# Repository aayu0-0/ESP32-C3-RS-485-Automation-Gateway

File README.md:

# ESP32-C3 RS-485 Automation Gateway

A compact, modular automation gateway designed around the **Seeed Studio XIAO ESP32-C3**, featuring RS-485 communication and a MikroE mikroBUS-compatible form factor.

This project focuses on developing a practical hardware platform for industrial communication and automation applications through iterative PCB design and prototyping.

## Project Overview

The project consists of three PCB design iterations (V1, V2 and V3), each introducing refinements to the schematic, component selection, power management, PCB layout and overall hardware integration.

The latest design uses the XIAO ESP32-C3 and follows a compact layout intended to fit the CEB-35/CEBV-35 enclosure.

## Hardware Specifications

- **Microcontroller:** Seeed Studio XIAO ESP32-C3
- **Communication:** RS-485
- **Expansion Interface:** MikroE mikroBUS form factor
- **Enclosure Compatibility:** CEB-35 / CEBV-35
- **PCB Design Software:** KiCad

## Design Iterations

### V1 – Initial Prototype
- Initial schematic and PCB development.
- RS-485 communication interface.
- Initial PCB layout and Gerber generation.

### V2 – Hardware Refinement
- Revised schematic and component selection.
- Improvements to power-related circuitry.
- Refinements to the RS-485 interface.
- Updated PCB design.

### V3 – Refined Design
- Integration of the Seeed Studio XIAO ESP32-C3.
- Refined PCB layout and component placement.
- Compact form factor.
- Enclosure-oriented design for CEB-35/CEBV-35.

## Repository Structure

```text
Home_Automation_Bengaluru/
│
├── V1/
│   ├── Schematic/
│   ├── PCB/
│   └── Gerbers/
│
├── V2/
│   ├── Schematic/
│   ├── PCB/
│   └── Manufacturing/
│
├── V3/
│   ├── Schematic/
│   ├── PCB/
│   └── Manufacturing/
│
├── Libraries/
│   └── Custom KiCad footprints and symbols
│
├── Datasheets/
│
└── README.md
```

*Directory names may vary according to the actual repository organization.*

## Software and Tools

- KiCad – Schematic capture and PCB layout.
- ESP32-C3 – Embedded processing platform.
- Git – Version control and project management.

## Getting Started

1. Clone the repository:

   ```bash
   git clone <repository-url>
   ```

2. Open the desired version's KiCad project.

3. Ensure the required custom footprints and libraries are available.

4. Review the schematic and PCB layout.

5. Refer to the Gerber and manufacturing files for PCB fabrication.

## Project Highlights

- Three generations of PCB development.
- ESP32-C3-based embedded platform.
- RS-485 communication capability.
- Modular mikroBUS-compatible design approach.
- Custom KiCad libraries and footprints.
- Enclosure-oriented PCB development.
- Version-controlled hardware development.

---

**Developed as part of an iterative hardware design and prototyping project.**

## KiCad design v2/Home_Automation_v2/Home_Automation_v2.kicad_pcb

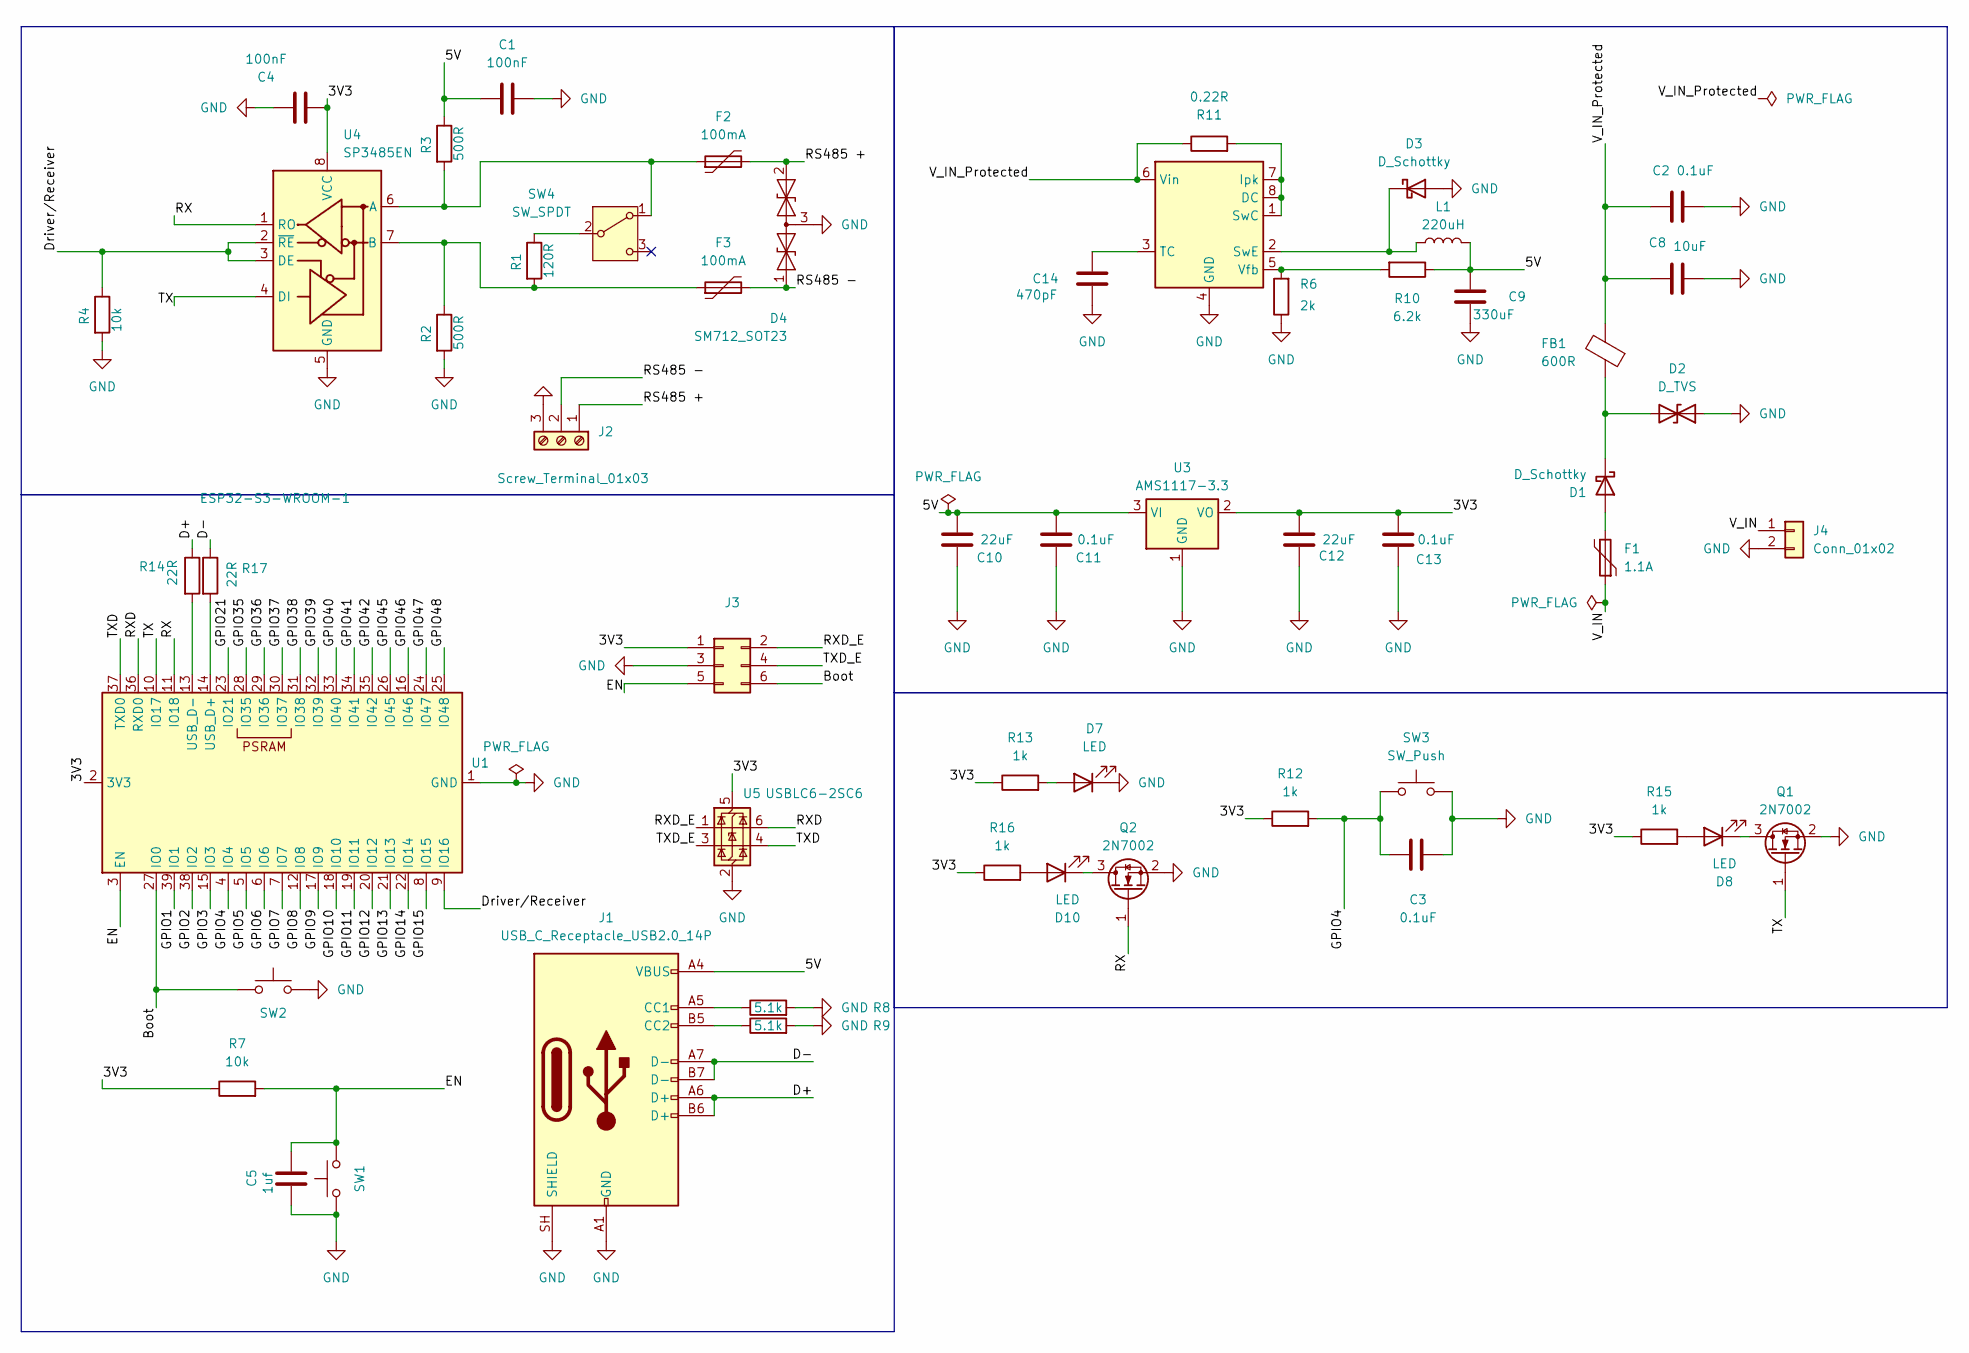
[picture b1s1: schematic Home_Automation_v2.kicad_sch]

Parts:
C1, C4: 100nF; C_0805_2012Metric_Pad1.18x1.45mm_HandSolder
C2, C3, C11, C13: 0.1uF; C_0805_2012Metric_Pad1.18x1.45mm_HandSolder
C5: 1uf; C_0805_2012Metric_Pad1.18x1.45mm_HandSolder
C8: 10uF; C_0805_2012Metric_Pad1.18x1.45mm_HandSolder
C9: 330uF; C_0805_2012Metric_Pad1.18x1.45mm_HandSolder
C10, C12: 22uF; C_0805_2012Metric_Pad1.18x1.45mm_HandSolder
C14: 470pF; C_0805_2012Metric_Pad1.18x1.45mm_HandSolder
D1, D3: D_Schottky; D_SMA
D2: D_TVS; D_SMA
D4: SM712_SOT23; SOT-23-3
D7, D8, D10: LED; LED_0805_2012Metric_Pad1.15x1.40mm_HandSolder
F1: 1.1A; Fuse_1206_3216Metric_Pad1.42x1.75mm_HandSolder
F2, F3: 100mA; Fuse_1206_3216Metric_Pad1.42x1.75mm_HandSolder
FB1: 600R; L_0805_2012Metric_Pad1.15x1.40mm_HandSolder
J1: USB_C_Receptacle_USB2.0_14P; USB_C_Receptacle_GCT_USB4105-xx-A_16P_TopMnt_Horizontal
J2: Screw_Terminal_01x03; TerminalBlock_Phoenix_MKDS-1,5-3_1x03_P5.00mm_Horizontal
J3: Conn_02x03_Odd_Even; PinHeader_2x03_P1.00mm_Vertical
J4: Conn_01x02; TerminalBlock_Phoenix_MKDS-1,5-2_1x02_P5.00mm_Horizontal
L1: 220uH; L_Bourns_SRR1210A
Q1, Q2: 2N7002; SOT-23
R1: 120R; R_0805_2012Metric_Pad1.20x1.40mm_HandSolder
R2, R3: 500R; R_0805_2012Metric_Pad1.20x1.40mm_HandSolder
R4, R7: 10k; R_0805_2012Metric_Pad1.20x1.40mm_HandSolder
R6: 2k; R_0805_2012Metric_Pad1.20x1.40mm_HandSolder
R8, R9: 5.1k; R_0805_2012Metric_Pad1.20x1.40mm_HandSolder
R10: 6.2k; R_0805_2012Metric_Pad1.20x1.40mm_HandSolder
R11: 0.22R; R_0805_2012Metric_Pad1.20x1.40mm_HandSolder
R12, R13, R15, R16: 1k; R_0805_2012Metric_Pad1.20x1.40mm_HandSolder
R14, R17: 22R; R_0805_2012Metric_Pad1.20x1.40mm_HandSolder
SW1, SW2, SW3: SW_Push; SW_SPST_B3S-1000
SW4: SW_SPDT; Nidec_Copal_CAS-120A
U1: ESP32-S3-WROOM-1
U2: MC34063AD; SOIC-8_3.9x4.9mm_P1.27mm
U3: AMS1117-3.3; SOT-223-3_TabPin2
U4: SP3485EN; SOIC-8_3.9x4.9mm_P1.27mm
U5: USBLC6-2SC6; SOT-23-6

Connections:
/3V3: C4.1, C12.2, C13.2, J3.1, R7.1, R12.1, R13.1, R15.1, R16.1, U1.2 (3V3), U3.2 (VO), U4.8 (VCC), U5.5 (VBUS)
/5V: C1.1, C9.2, C10.2, C11.2, J1.A4 (VBUS), J1.A9 (VBUS), J1.B4 (VBUS), J1.B9 (VBUS), L1.2, R3.1, R10.1, U3.3 (VI)
/Boot: J3.6, SW2.1, U1.27 (IO0)
/D+: J1.A6 (D+), J1.B6 (D+), R14.1
/D-: J1.A7 (D-), J1.B7 (D-), R17.1
/Driver/Receiver: R4.1, U1.9 (IO16), U4.2 (~RE), U4.3 (DE)
/EN: C5.1, J3.5, R7.2, SW1.2, U1.3 (EN)
/GPIO1: U1.39 (IO1)
/GPIO2: U1.38 (IO2)
/GPIO3: U1.15 (IO3)
/GPIO4: C3.2, R12.2, SW3.1, U1.4 (IO4)
/GPIO5: U1.5 (IO5)
/GPIO6: U1.6 (IO6)
/GPIO7: U1.7 (IO7)
/GPIO8: U1.12 (IO8)
/GPIO9: U1.17 (IO9)
/GPIO10: U1.18 (IO10)
/GPIO11: U1.19 (IO11)
/GPIO12: U1.20 (IO12)
/GPIO13: U1.21 (IO13)
/GPIO14: U1.22 (IO14)
/GPIO15: U1.8 (IO15)
/GPIO21: U1.23 (IO21)
/GPIO35: U1.28 (IO35)
/GPIO36: U1.29 (IO36)
/GPIO37: U1.30 (IO37)
/GPIO38: U1.31 (IO38)
/GPIO39: U1.32 (IO39)
/GPIO40: U1.33 (IO40)
/GPIO41: U1.34 (IO41)
/GPIO42: U1.35 (IO42)
/GPIO45: U1.26 (IO45)
/GPIO46: U1.16 (IO46)
/GPIO47: U1.24 (IO47)
/GPIO48: U1.25 (IO48)
/RS485 +: D4.2 (A2), F2.2, J2.1
/RS485 -: D4.1 (A1), F3.2, J2.2
/RX: Q2.1 (G), U1.11 (IO18), U4.1 (RO)
/RXD: U1.36 (RXD0), U5.6 (I/O1)
/RXD_E: J3.2, U5.1 (I/O1)
/TX: Q1.1 (G), U1.10 (IO17), U4.4 (DI)
/TXD: U1.37 (TXD0), U5.4 (I/O2)
/TXD_E: J3.4, U5.3 (I/O2)
/V_IN: F1.1, J4.1
/V_IN_Protected: C2.2, C8.2, FB1.2, R11.1, U2.6 (Vin)
GND: C1.2, C2.1, C3.1, C4.2, C5.2, C8.1, C9.1, C10.1, C11.1, C12.1, C13.1, C14.2, D2.1 (A1), D3.2 (A), D4.3 (common), D7.1 (K), J1.A1 (GND), J1.A12 (GND), J1.B1 (GND), J1.B12 (GND), J1.SH (SHIELD), J2.3, J3.3, J4.2, Q1.2 (S), Q2.2 (S), R2.2, R4.2, R6.1, R8.2, R9.2, SW1.1, SW2.2, SW3.2, U1.1 (GND), U1.40 (GND), U1.41 (GND), U2.4 (GND), U3.1 (GND), U4.5 (GND), U5.2 (GND)
unnamed: D1.2 (A), F1.2
unnamed: D1.1 (K), D2.2 (A2), FB1.1
unnamed: D3.1 (K), L1.1, U2.2 (SwE)
unnamed: D7.2 (A), R13.2
unnamed: D8.2 (A), R15.2
unnamed: D8.1 (K), Q1.3 (D)
unnamed: D10.2 (A), R16.2
unnamed: D10.1 (K), Q2.3 (D)
unnamed: J1.A5 (CC1), R8.1
unnamed: J1.B5 (CC2), R9.1
unnamed: F2.1, R3.2, SW4.1 (A), U4.6 (A)
unnamed: R1.1, SW4.2 (B)
unnamed: R17.2, U1.14 (USB_D+)
unnamed: R14.2, U1.13 (USB_D-)
unnamed: R11.2, U2.1 (SwC), U2.7 (Ipk), U2.8 (DC)
unnamed: C14.1, U2.3 (TC)
unnamed: R6.2, R10.2, U2.5 (Vfb)
unnamed: F3.1, R1.2, R2.1, U4.7 (B)

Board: 2 copper layers, 55 parts (0 on the bottom side), 37 nets, no tracks yet.

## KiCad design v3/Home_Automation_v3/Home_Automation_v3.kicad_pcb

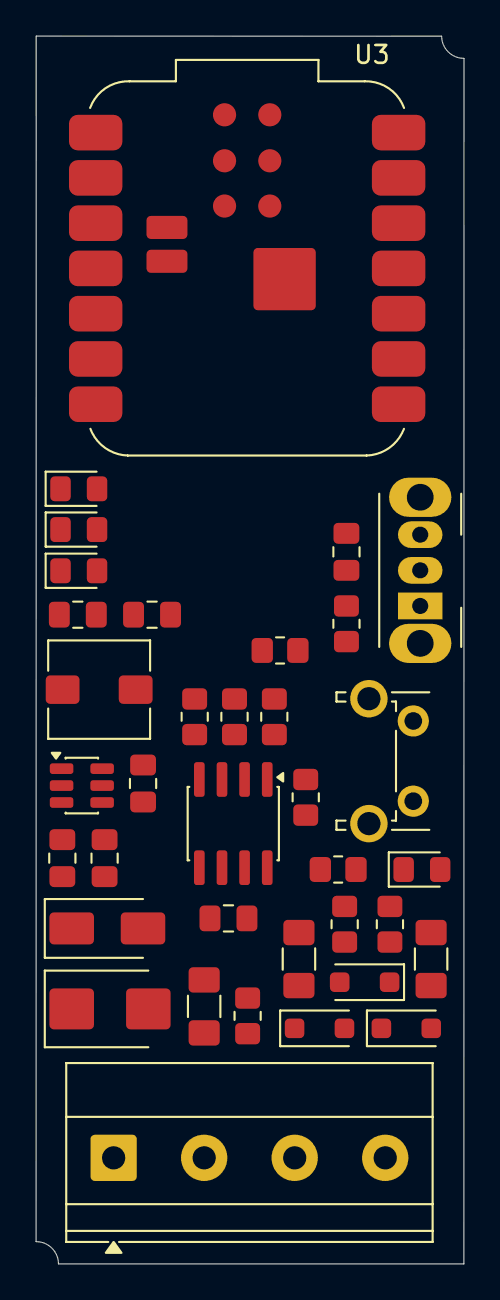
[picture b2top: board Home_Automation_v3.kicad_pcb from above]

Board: 2 copper layers, 24.0 x 68.9 mm, 36 parts (0 on the bottom side), 22 nets, no tracks yet.

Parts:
C1: 10uF; C_0805_2012Metric_Pad1.18x1.45mm_HandSolder
C2, C6: 100nF; C_0805_2012Metric_Pad1.18x1.45mm_HandSolder
C3, C4, C7: 22uF; C_0805_2012Metric_Pad1.18x1.45mm_HandSolder
C5: 0.1uF; C_0805_2012Metric_Pad1.18x1.45mm_HandSolder
D1, D2, D3, D4: LED; LED_0805_2012Metric_Pad1.15x1.40mm_HandSolder
D5, D6, D7: SMF12CA; D_SOD-123F
D8: SMBJ15A; D_SMB
D9: SS34; D_SMA
F1, F2, F3: Polyfuse; Fuse_1206_3216Metric_Pad1.42x1.75mm_HandSolder
J4: Screw_Terminal_01x04; TerminalBlock_Phoenix_MKDS-1,5-4-5.08_1x04_P5.08mm_Horizont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
L1: 3.3uH; L_Wuerth_HCI-5040
R1, R4, R10: 10k; R_0805_2012Metric_Pad1.20x1.40mm_HandSolder
R2, R3: 33R; R_0805_2012Metric_Pad1.20x1.40mm_HandSolder
R5: 330R; R_0805_2012Metric_Pad1.20x1.40mm_HandSolder
R6: 660; R_0805_2012Metric_Pad1.20x1.40mm_HandSolder
R7: 120R; R_0805_2012Metric_Pad1.20x1.40mm_HandSolder
R8, R9: 680R; R_0805_2012Metric_Pad1.20x1.40mm_HandSolder
SW1: SW_Push; SW_Tactile_SPST_Angled_PTS645Vx58-2LFS
SW2: SW_SPDT; SW_Slide_SPDT_Angled_CK_OS102011MA1Q
U1: AP63203WU; TSOT-23-6
U2: SP3485EN; SOIC-8_3.9x4.9mm_P1.27mm
U3: XIAO_ESP32C3; MCU_Seeed_ESP32C3

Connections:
/3V3: C3.2, C4.2, C5.2, L1.2, R4.1, R9.1, SW2.3 (C), U1.1 (FB), U2.8 (VCC)
/12V: C1.1, C7.1, D9.1 (K), U1.2 (EN), U1.3 (IN)
/D6: R1.1, U2.2 (~RE), U2.3 (DE), U3.7 (D6)
/EX 12V: F3.1, J4.2, R6.1
/INT: SW1.2, U3.1 (D0)
/RS485_A: D5.2 (A2), D6.2 (A2), F1.2, J4.3
/RS485_B: D5.1 (A1), D7.1 (A1), F2.2, J4.4
/RX: D4.2 (A), R2.2, U3.5 (D4)
/TX: D3.2 (A), R3.2, U3.6 (D5)
GND: C1.2, C3.1, C4.1, C5.1, C6.1, C7.2, D1.1 (K), D2.1 (K), D3.1 (K), D4.1 (K), D6.1 (A1), D7.2 (A2), D8.1 (A1), J4.1, R1.2, R8.2, R10.2, U1.4 (GND), U2.5 (GND), U3.13 (GND)
unnamed: D1.2 (A), R5.2
unnamed: D2.2 (A), R6.2
unnamed: D8.2 (A2), D9.2 (A), F3.2
unnamed: C6.2, SW2.2 (B), U3.12 (3V3)
unnamed: R5.1, SW1.1
unnamed: R10.1, SW2.1 (A)
unnamed: C2.1, U1.6 (BST)
unnamed: C2.2, L1.1, U1.5 (SW)
unnamed: F1.1, R7.2, R9.2, U2.6 (A)
unnamed: F2.1, R7.1, R8.1, U2.7 (B)
unnamed: R3.1, U2.4 (DI)
unnamed: R2.1, R4.2, U2.1 (RO)
